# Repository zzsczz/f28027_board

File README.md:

# f28027_board
tms320f28027  board;    pin compitable with ti's f28027 launchpad ;

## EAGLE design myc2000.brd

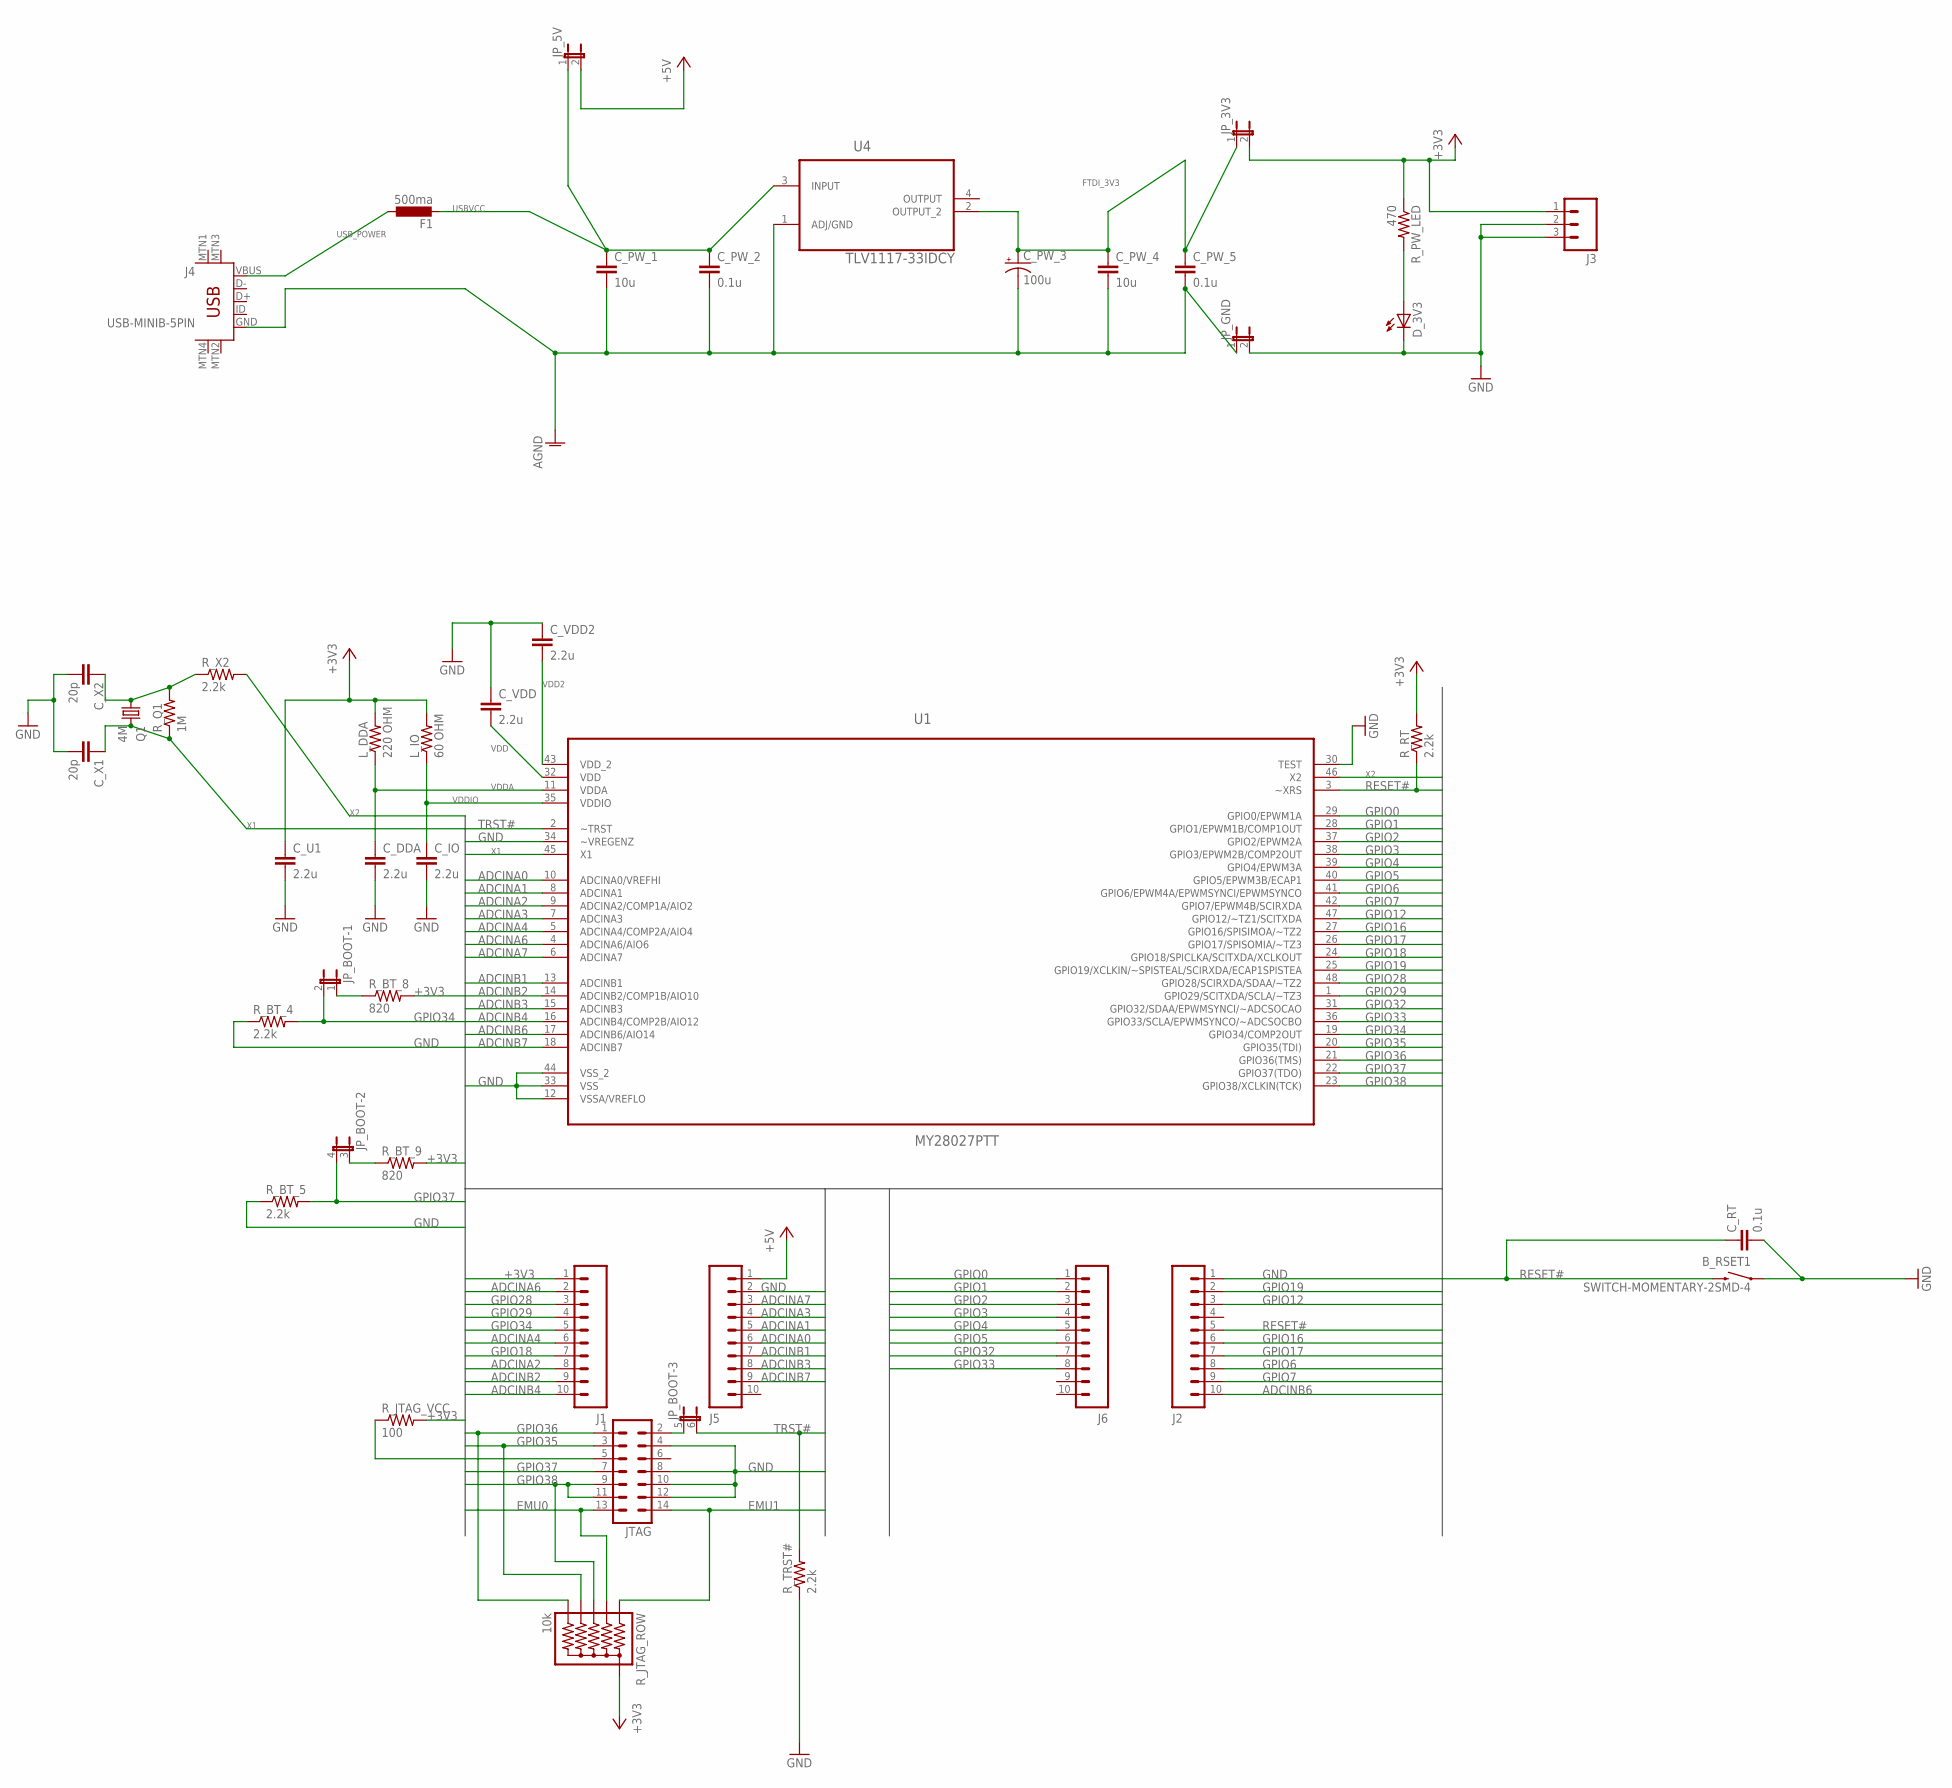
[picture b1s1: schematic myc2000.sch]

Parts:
B_RSET1: SWITCH-MOMENTARY-2SMD-4; TACTILE_SWITCH_TALL
C_DDA: 2.2u; 0805
C_IO: 2.2u; 0805
C_PW_1, C_PW_4: 10u; 0805
C_PW_2, C_PW_5: 0.1u; 0805
C_PW_3: 100u; EIA3528
C_RT: 0.1u; 0805
C_U1: 2.2u; 0805
C_VDD, C_VDD2: 2.2u; 0805
C_X1, C_X2: 20p; 0603-CAP
D_3V3: LEDSML0805; SML0805
F1: 500ma; L1812
J1, J2, J5, J6: M10NO_SILK_PTH_FEMALE; 1X10_NO_SILK
J3: M031X03_NO_SILK; 1X03_NO_SILK
J4: USB-MINIB-5PIN; USB-MINIB
JP_3V3, JP_5V: JP1E; JP1
JP_BOOT: JP3QE; JP3Q
JP_GND: JP1E; JP1
JTAG: MA07-2
L_DDA: 220 OHM; 0603-RES
L_IO: 60 OHM; 0805
Q1: 4M; HC49UP
R_BT_4, R_BT_5: 2.2k; 0805
R_BT_8, R_BT_9: 820; 0805
R_JTAG_ROW: 10k; RPACK-SIP-PTH-5
R_JTAG_VCC: 100; 0805
R_PW_LED: 470; 0805
R_Q1: 1M; 0603-RES
R_RT: 2.2k; 0805
R_TRST#: 2.2k; 0805
R_X2: 2.2k; 0603-RES
U1: MY28027PTT; QFP50P900X900X160-48N
U4: TLV1117-33IDCY; SOT230P700X180-4N

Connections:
+3V3: C_U1.1, J1.1, J3.1, JP_3V3.2, L_DDA.2, L_IO.2, R_BT_8.2, R_BT_9.2, R_JTAG_ROW.P$1 (1), R_JTAG_VCC.2, R_PW_LED.1, R_RT.2
+5V: J5.1, JP_5V.2
ADCINA0: J5.6, U1.10 (ADCINA0/VREFHI)
ADCINA1: J5.5, U1.8 (ADCINA1)
ADCINA2: J1.8, U1.9 (ADCINA2/COMP1A/AIO2)
ADCINA3: J5.4, U1.7 (ADCINA3)
ADCINA4: J1.6, U1.5 (ADCINA4/COMP2A/AIO4)
ADCINA6: J1.2, U1.4 (ADCINA6/AIO6)
ADCINA7: J5.3, U1.6 (ADCINA7)
ADCINB1: J5.7, U1.13 (ADCINB1)
ADCINB2: J1.9, U1.14 (ADCINB2/COMP1B/AIO10)
ADCINB3: J5.8, U1.15 (ADCINB3)
ADCINB4: J1.10, U1.16 (ADCINB4/COMP2B/AIO12)
ADCINB6: J2.10, U1.17 (ADCINB6/AIO14)
ADCINB7: J5.9, U1.18 (ADCINB7)
AGND: C_PW_1.2, C_PW_2.2, C_PW_3.C (-), C_PW_4.2, C_PW_5.2, J4.GND, JP_GND.1, U4.1 (ADJ/GND)
EMU0: JTAG.13, R_JTAG_ROW.P$3 (3)
EMU1: JTAG.14, R_JTAG_ROW.P$2 (2)
FTDI_3V3: C_PW_3.A (+), C_PW_4.1, C_PW_5.1, JP_3V3.1, U4.2 (OUTPUT_2)
GND: B_RSET1.A2 (1), C_DDA.2, C_IO.2, C_RT.2, C_U1.2, C_VDD.1, C_VDD2.1, C_X1.2, C_X2.2, D_3V3.C, J2.1, J3.2, J3.3, J5.2, JP_GND.2, JTAG.4, JTAG.8, JTAG.10, JTAG.12, R_BT_4.1, R_BT_5.1, R_TRST#.1, U1.12 (VSSA/VREFLO), U1.30 (TEST), U1.33 (VSS), U1.34 (~VREGENZ), U1.44 (VSS_2)
GPIO0: J6.1, U1.29 (GPIO0/EPWM1A)
GPIO1: J6.2, U1.28 (GPIO1/EPWM1B/COMP1OUT)
GPIO2: J6.3, U1.37 (GPIO2/EPWM2A)
GPIO3: J6.4, U1.38 (GPIO3/EPWM2B/COMP2OUT)
GPIO4: J6.5, U1.39 (GPIO4/EPWM3A)
GPIO5: J6.6, U1.40 (GPIO5/EPWM3B/ECAP1)
GPIO6: J2.8, U1.41 (GPIO6/EPWM4A/EPWMSYNCI/EPWMSYNCO)
GPIO7: J2.9, U1.42 (GPIO7/EPWM4B/SCIRXDA)
GPIO12: J2.3, U1.47 (GPIO12/~TZ1/SCITXDA)
GPIO16: J2.6, U1.27 (GPIO16/SPISIMOA/~TZ2)
GPIO17: J2.7, U1.26 (GPIO17/SPISOMIA/~TZ3)
GPIO18: J1.7, U1.24 (GPIO18/SPICLKA/SCITXDA/XCLKOUT)
GPIO19: J2.2, U1.25 (GPIO19/XCLKIN/~SPISTEAL/SCIRXDA/ECAP1SP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)
GPIO28: J1.3, U1.48 (GPIO28/SCIRXDA/SDAA/~TZ2)
GPIO29: J1.4, U1.1 (GPIO29/SCITXDA/SCLA/~TZ3)
GPIO32: J6.7, U1.31 (GPIO32/SDAA/EPWMSYNCI/~ADCSOCAO)
GPIO33: J6.8, U1.36 (GPIO33/SCLA/EPWMSYNCO/~ADCSOCBO)
GPIO34: J1.5, JP_BOOT.2, R_BT_4.2, U1.19 (GPIO34/COMP2OUT)
GPIO35: JTAG.3, R_JTAG_ROW.P$5 (5), U1.20 (GPIO35(TDI))
GPIO36: JTAG.1, R_JTAG_ROW.P$6 (6), U1.21 (GPIO36(TMS))
GPIO37: JP_BOOT.4 (2), JTAG.7, R_BT_5.2, U1.22 (GPIO37(TDO))
GPIO38: JTAG.9, JTAG.11, R_JTAG_ROW.P$4 (4), U1.23 (GPIO38/XCLKIN(TCK))
JTAG_TRST: JP_BOOT.5 (1), JTAG.2
unnamed: D_3V3.A, R_PW_LED.2
unnamed: JP_BOOT.3 (1), R_BT_9.1
unnamed: JP_BOOT.1, R_BT_8.1
unnamed: JTAG.5, R_JTAG_VCC.1
RESET#: B_RSET1.B2 (2), C_RT.1, J2.5, R_RT.1, U1.3 (~XRS)
TRST#: JP_BOOT.6 (2), R_TRST#.2, U1.2 (~TRST)
USBVCC: C_PW_1.1, C_PW_2.1, F1.2, JP_5V.1, U4.3 (INPUT)
USB_POWER: F1.1, J4.VBUS
VDD: C_VDD.2, U1.32 (VDD)
VDD2: C_VDD2.2, U1.43 (VDD_2)
VDDA: C_DDA.1, L_DDA.1, U1.11 (VDDA)
VDDIO: C_IO.1, L_IO.1, U1.35 (VDDIO)
X1: C_X1.1, Q1.2, R_Q1.1, U1.45 (X1)
X2: R_X2.2, U1.46 (X2)
X2_2: C_X2.1, Q1.1, R_Q1.2, R_X2.1

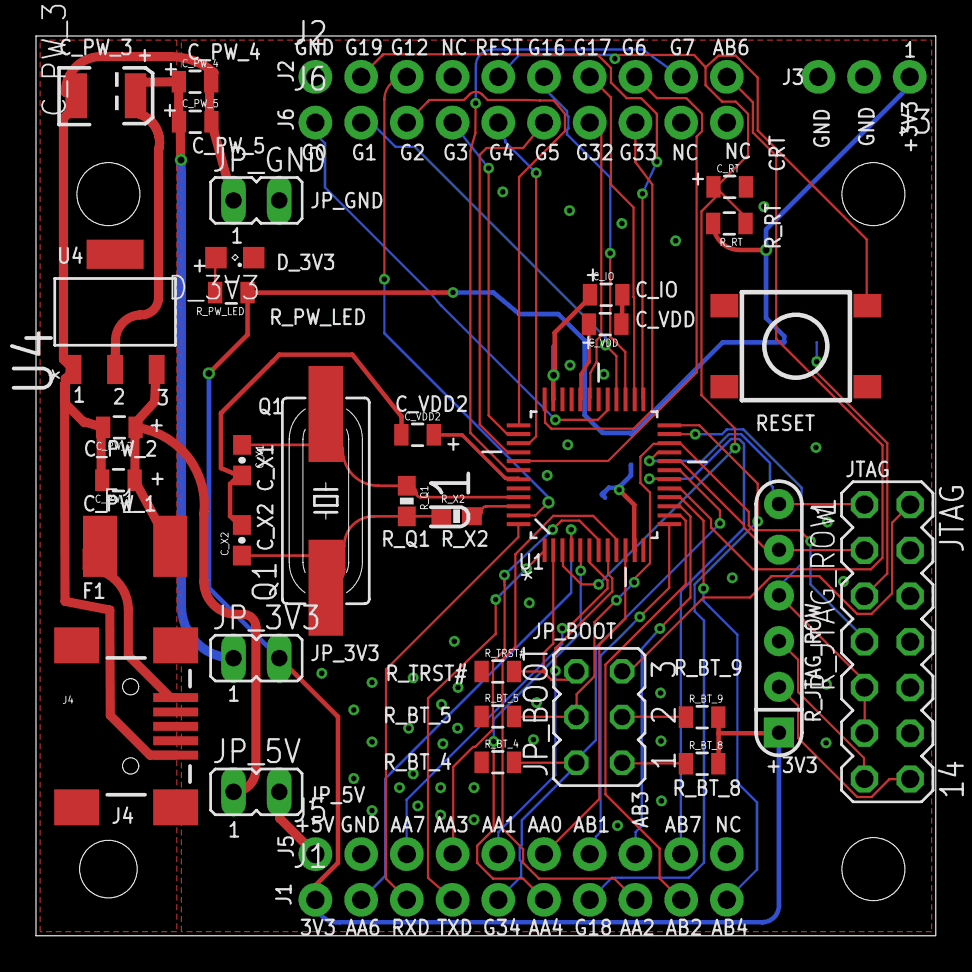
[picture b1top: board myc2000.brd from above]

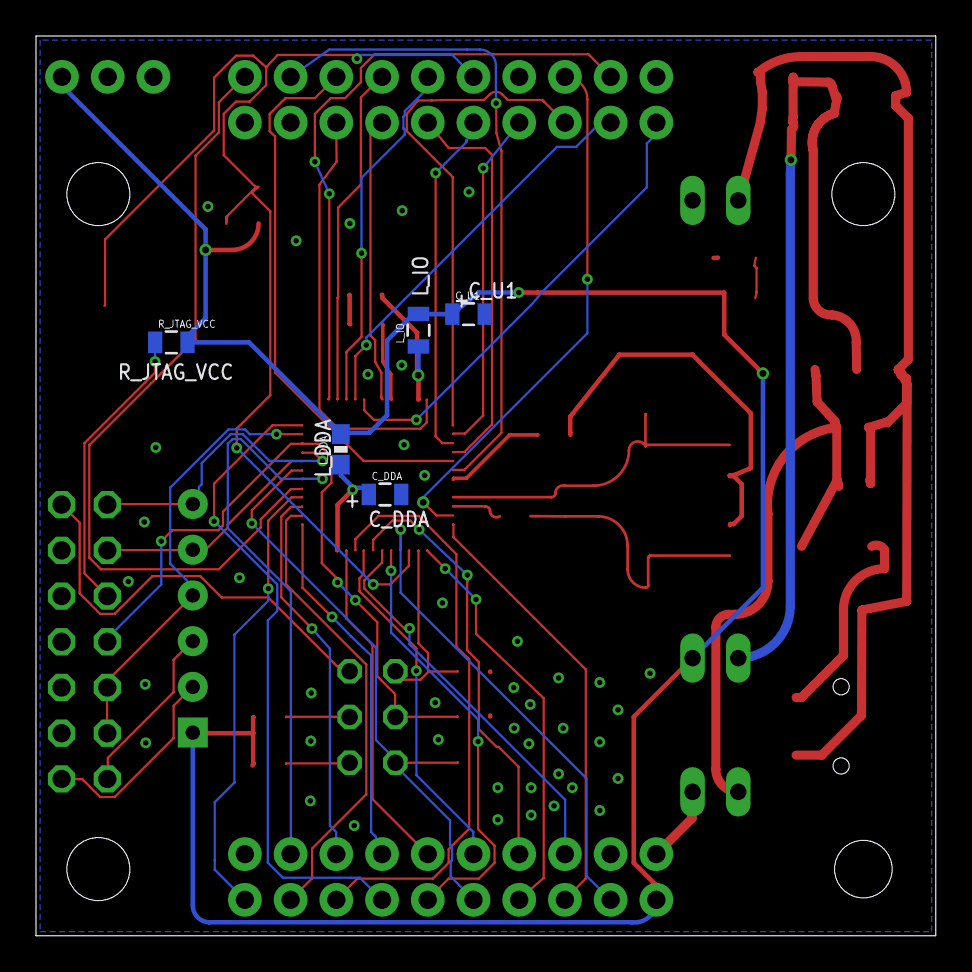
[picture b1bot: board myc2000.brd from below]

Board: 2 copper layers, 50.0 x 50.0 mm, 43 parts (5 on the bottom side), 58 nets.

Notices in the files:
parts and their libraries:
SparkFun-Electromechanical: Licensing: Creative Commons ShareAlike 4.0 International - https://creativecommons.org/licenses/by-sa/4.0
